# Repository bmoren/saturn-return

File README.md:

# saturn-return
Send transmissions, listen for communication

## ** REV2 boards are  currently untested **

Modular level > stereo line out &amp; stereo aux send mixer (a friend of norns)
4hp

Modular Left and Right signals are fed through a voltage divider, tuned, and sent out into space.      
Transmissions are received as stereo line signals.     
Transmissions are tuned and combined with signals (for recording and archiving).    

An module and idea based on [discussion in the norns I/O thread](https://llllllll.co/t/norns-audio-in-out-specs/30256/37?u=bmoren)

[View it on ModularGrid](https://www.modulargrid.net/e/other-unknown-saturn-return)

## I/O

Inputs:
+ L/R modular level signals
+ Line input

Outputs: 
+ Stereo line output
+ Stereo mix line output (mixed inputs)

Knobs:
+ Level control for modular input to mix
+ Level control for line input to mix

Pin headers:
support alternative I/O configurations, non-eurorack builds, and general experimentation!

## Build Instructions
1. (optional advanced preperation – use your multimeter to find matched resistor values R3=R7, R4=R8, R1=R2=R5=R6 )
1. Start with the resistors, place them into the footrpints
1. Solder resistors, clip the legs
1. Place jacks and pots into the footprints. * do not solder them yet!
1. Place the panel on, screw down jacks and pots to the panel (this will align everything)
1. finally solder the jacks and panels
1. attach knobs
1. done!

## BOM
+ 2X [Thonkiconn Jacks](https://www.thonk.co.uk/shop/3-5mm-jacks/)
+ 3X [Thonkiconn Stereo Jacks](https://www.thonk.co.uk/shop/3-5mm-jacks/)
+ 2X [Alpha A10k dual gang potentiometers](https://www.thonk.co.uk/shop/alpha-9mm-pots-dshaft/)
+ 4X 10k Resistor
+ 2X 1k Resistor
+ 2X 2.2k Resistor
+ Optional: 4X 3 position 2.54mm pin header

## license 

CC BY-SA 4.0     
Build and use at your own risk! I am not responsible for any damage to self or otherwise that arises from using this project!

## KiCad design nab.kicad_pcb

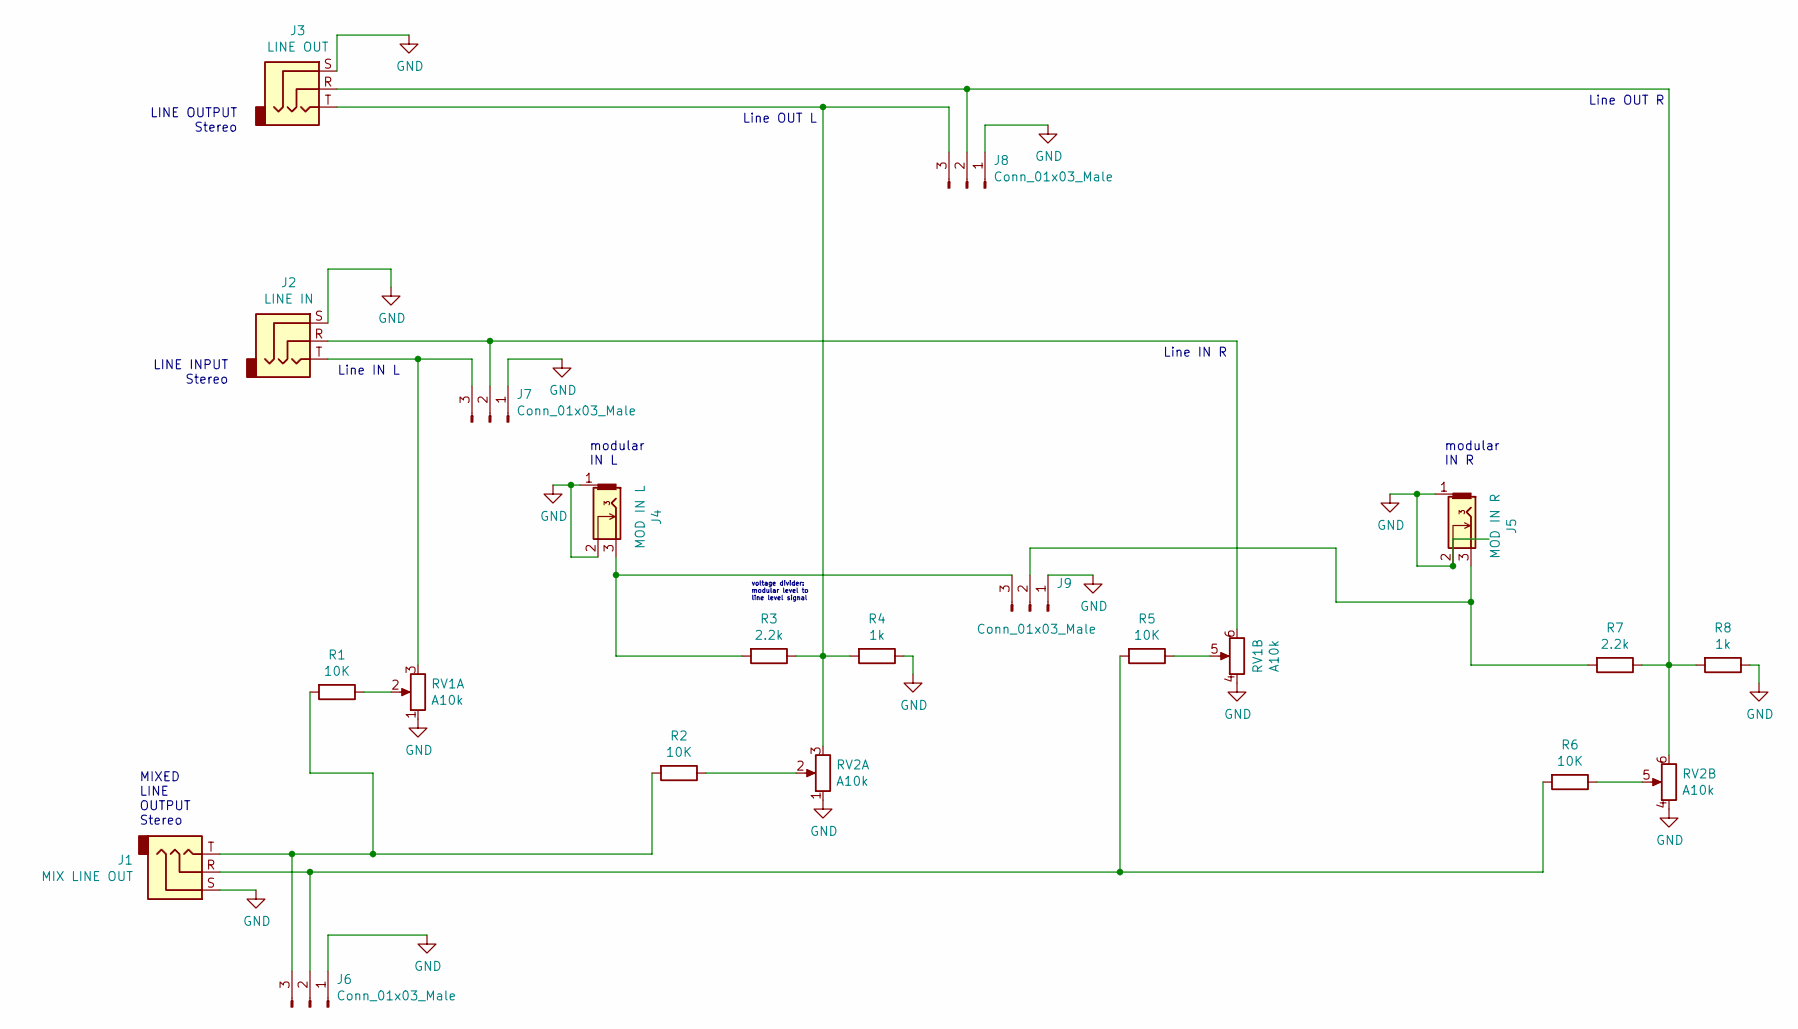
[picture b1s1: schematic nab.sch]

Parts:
J1: MIX LINE OUT; Thonkiconn_stereo_small_holes
J2: LINE IN; Thonkiconn_stereo_small_holes
J3: LINE OUT; Thonkiconn_stereo_small_holes
J4: MOD IN L; Thonkiconn_small_holes
J5: MOD IN R; Thonkiconn_small_holes
J6, J7, J8, J9: Conn_01x03_Male; PinHeader_1x03_P2.54mm_Vertical
R1, R2, R5, R6: 10K; R_Axial_DIN0207_L6.3mm_D2.5mm_P7.62mm_Horizontal
R3, R7: 2.2k; R_Axial_DIN0207_L6.3mm_D2.5mm_P7.62mm_Horizontal
R4, R8: 1k; R_Axial_DIN0207_L6.3mm_D2.5mm_P7.62mm_Horizontal
RV1, RV2: A10k; Potentiometer_Alpha_RD902F-40-00D_Dual_Vertical

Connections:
GND: J1.S, J2.S, J3.S, J4.1, J4.2, J5.1, J5.2, J6.1, J7.1, J8.1, J9.1, R4.1, R8.1, RV1.1, RV1.4, RV2.1, RV2.4
unnamed: J1.R, J6.2, R5.2, R6.2
unnamed: J1.T, J6.3, R1.2, R2.2
unnamed: J2.R, J7.2, RV1.6
unnamed: J2.T, J7.3, RV1.3
unnamed: J3.R, J8.2, R7.1, R8.2, RV2.6
unnamed: J3.T, J8.3, R3.1, R4.2, RV2.3
unnamed: J4.3, J9.3, R3.2
unnamed: J5.3, J9.2, R7.2
unnamed: R1.1, RV1.2
unnamed: R2.1, RV2.2
unnamed: R5.1, RV1.5
unnamed: R6.1, RV2.5

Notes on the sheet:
modular IN R
Line OUT L
Line IN R
MIXED LINE OUTPUT Stereo
LINE OUTPUT Stereo
voltage divider: modular level to line level signal
modular IN L
LINE INPUT Stereo
Line IN L
Line OUT R

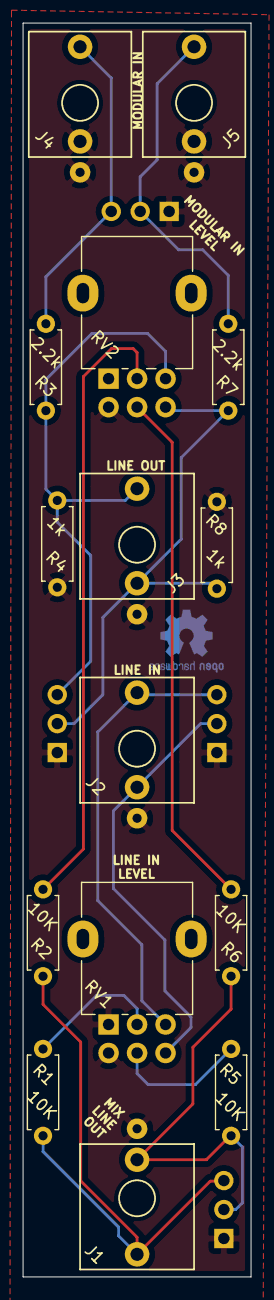
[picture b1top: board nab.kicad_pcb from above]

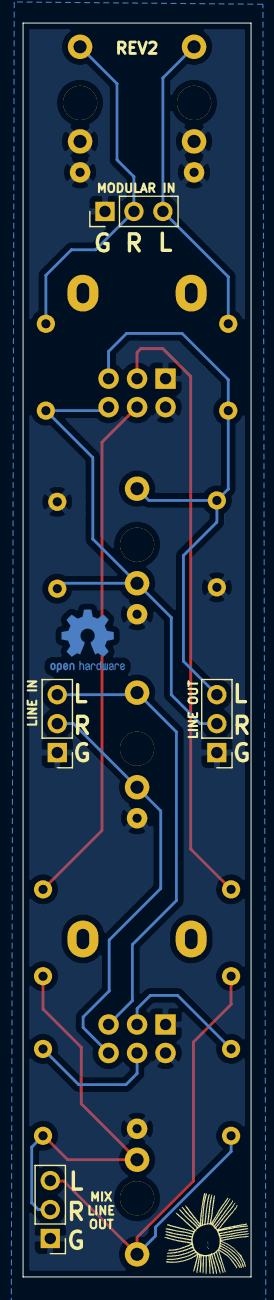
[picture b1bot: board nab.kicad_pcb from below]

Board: 2 copper layers, 20.0 x 110.0 mm, 19 parts (4 on the bottom side), 13 nets.

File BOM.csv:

"Source:","/Users/bmoren/Desktop/module development/saturn return/nab.sch"
"Date:","Tuesday, November 24, 2020 at 02:54:47 PM"
"Tool:","Eeschema (5.1.6-0-10_14)"
"Generator:","/Applications/KiCad/kicad.app/Contents/SharedSupport/plugins/bom_csv_grouped_by_value_with_fp.py"
"Component Count:","19"
"Ref","Qnty","Value","Cmp name","Footprint","Description","Vendor"
"J1, ","1","MIX LINE OUT","AudioJack3","modular:Thonkiconn_stereo_small_holes","Audio Jack, 3 Poles (Stereo / TRS)",""
"J2, ","1","LINE IN","AudioJack3","modular:Thonkiconn_stereo_small_holes","Audio Jack, 3 Poles (Stereo / TRS)",""
"J3, ","1","LINE OUT","AudioJack3","modular:Thonkiconn_stereo_small_holes","Audio Jack, 3 Poles (Stereo / TRS)",""
"J4, ","1","MOD IN L","thonkiconn","modular:Thonkiconn_small_holes","2-pin audio jack receptable (mono/TS connector) with switching contact",""
"J5, ","1","MOD IN R","thonkiconn","modular:Thonkiconn_small_holes","2-pin audio jack receptable (mono/TS connector) with switching contact",""
"J6, J7, J8, J9, ","4","Conn_01x03_Male","Conn_01x03_Male","Connector_PinHeader_2.54mm:PinHeader_1x03_P2.54mm_Vertical","Generic connector, single row, 01x03, script generated (kicad-library-utils/schlib/autogen/connector/)",""
"R1, R2, R5, R6, ","4","10K","R","Resistor_THT:R_Axial_DIN0207_L6.3mm_D2.5mm_P7.62mm_Horizontal","Resistor",""
"R3, R7, ","2","2.2k","R","Resistor_THT:R_Axial_DIN0207_L6.3mm_D2.5mm_P7.62mm_Horizontal","Resistor",""
"R4, R8, ","2","1k","R","Resistor_THT:R_Axial_DIN0207_L6.3mm_D2.5mm_P7.62mm_Horizontal","Resistor",""
"RV1, RV2, ","2","A10k","R_POT_Dual_Separate","Potentiometer_THT:Potentiometer_Alpha_RD902F-40-00D_Dual_Vertical","Dual potentiometer, separate units",""

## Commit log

2020-11-24 init
2020-11-24 clean1
2020-11-25 add schematic pdf
2020-12-03 rev2 (missed a ground)
2020-12-13 instructions
2020-12-13 rev2
2020-12-13 add rev2 gerbs (untested)
